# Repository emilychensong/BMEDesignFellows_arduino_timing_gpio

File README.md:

# Lab: EDA - Arduino Nano Every with LED and Button

## Fork Git Repository

1. Fork this GitLab repository into your userspace.
1. Add Dr. Palmeri (`mlp6`) as a Maintainer of your forked repository.  He will add the TAs and graders as Developers to this project for you.
1. Clone your version of the repository to your local computer.
1. Take note of:
    - The contents of [.gitignore](.gitignore) to exclude files that KiCad will create that should *not* be included in the git repository.
    - The existence of a `.gitlab-ci.yml` file to automatically build and test your project.
    - The existence of files for a KiCad project.

## Modify the Schematic

1. Update the schematic metadata with your name and add a fun logo.
1. Move the battery off-board and connect it to the `VIN` and `GND` pins on the Arduino Nano Every with a 2-pin socket connector.
1. Exclude the battery (`BT1`), the push buttont swith (`SW1`), and the LED (`D1`), along with all of their directly-connected socket connectors from the schematic (leave the pin connectors on the board).
1. Add a second `EYE` LED driven by the same `LED_OUT` signal.
1. Add another LED driven by `D5` on a net called `NOSE_LED_OUT`.
1. Add 4 mounting holes that can accomodate M3 bolts to your schematic that are not electrically connected.
1. Make sure that your schematic passes ERC.
1. Update the `Rev #` in the document metadata to `v1.1.0`.
1. Create a git commit of your modified schematic, give it an annotated tag of
`v1.1.0` and push it to your GitLab repository.
1. Upload a zip archive of your `v1.1.0` tagged repository to Gradescope.  You can download a zip of the repository on the Gitlab web interface with an option in the blue `Code` button.

## Add and SPICE Model an Analog Input

We will modulate an analog input to the `A0` pin of the Arduino Nano Every with
a potentiometer to allow a user to modulate the brightness of the LED.

1. On the `Inputs` sheet, add a potentiometer (`POT1`) with a 20 k$\Omega$
resistance and a fixed 10k$\Omega$ series resistance to create a voltage divider
of a `+5V` regulated output voltage from the Arduino Nano.
1. Connect the voltage across the potentiometer to the `A0` pin of the Arduino
Nano Every, with a Net Label called `BRIGHT_IN`.
1. Simulate the voltage on the `BRIGHT_IN` net for the minimum and maximum
resistance of `POT1`.
1. Is this voltage linear with changes in `POT1` resistance?
1. Adjust your fixed resistance to:
    - Ensure that the voltage on `BRIGHT_IN` never exceeds 3.3 V, and
    - Optimize the dynamic range of the potentiemeter to be as large as possible (i.e., make the slope of the voltage change as a function of resistance change as great as possible).
1. Include a screenshot of your final simulated `BRIGHT_IN` voltage in the `Inputs` schematic sheet.
1. Update the `Rev #` in the document metadata to `v1.2.0`.
1. Commit your updated schematic with the model and its results and tag it `v1.2.0`.
1. Push your commits and annotated tags to your GitLab repository.
1. Upload a zip archive of your `v1.2.0` tagged repository to Gradescope.

## Layout a Single-Sided PCB

Next you will create a PCB from the schematic that you captured last week.

1. Assign footprints to all parts in your schematic.
    - All resistors and capacitors and other passive components should be THT.
    - Your pins and sockets should be 2.54 mm vertical orientation (`Pin Socket:1x02,P2.54mm,Vertical`) to allow external wires to be attached to your PCB.
1. The **Design Rules** (`*.kicad_dru`) file in the repository will impose these constraints:
    - Trace width $\geq$ 20 mil
    - Clearance $\geq$ 32 mil
    - Drill diameter $\geq$ 1 mm
1. Set your **Page Settings** for the sheet footer metadata.
1. Your board should be single-sided.
1. Optimize the size of your board to be as small as possible in your layout (as outlined with `Edge.Cuts`).
1. Place mounting holes on each corner of the board, no closer than 2 mm to any edge.
1. Remember that THT component bodies should be on the *opposite* side of the board from their traces (in contrast to SMD components).
1. Use filled ground pours where possible.
1. Make sure that your schematic passes the **Design Rules Check (DRC)**.
1. Commit your PCB layout to your repository and tag it `v1.3.0`.
1. Push your commits and annotated tags to your GitLab repository.
1. Upload a zip archive of your `v1.2.0` tagged repository to Gradescope.

## What to Submit

- Make sure that all of your local git repository commits and annotated tags
have been pushed to GitLab.
- Make sure that Dr. Palmeri and the TAs are Maintainers of your forked
repository.
- Upload a zip archives of your tagged repository to Gradescope for each section
of this lab.

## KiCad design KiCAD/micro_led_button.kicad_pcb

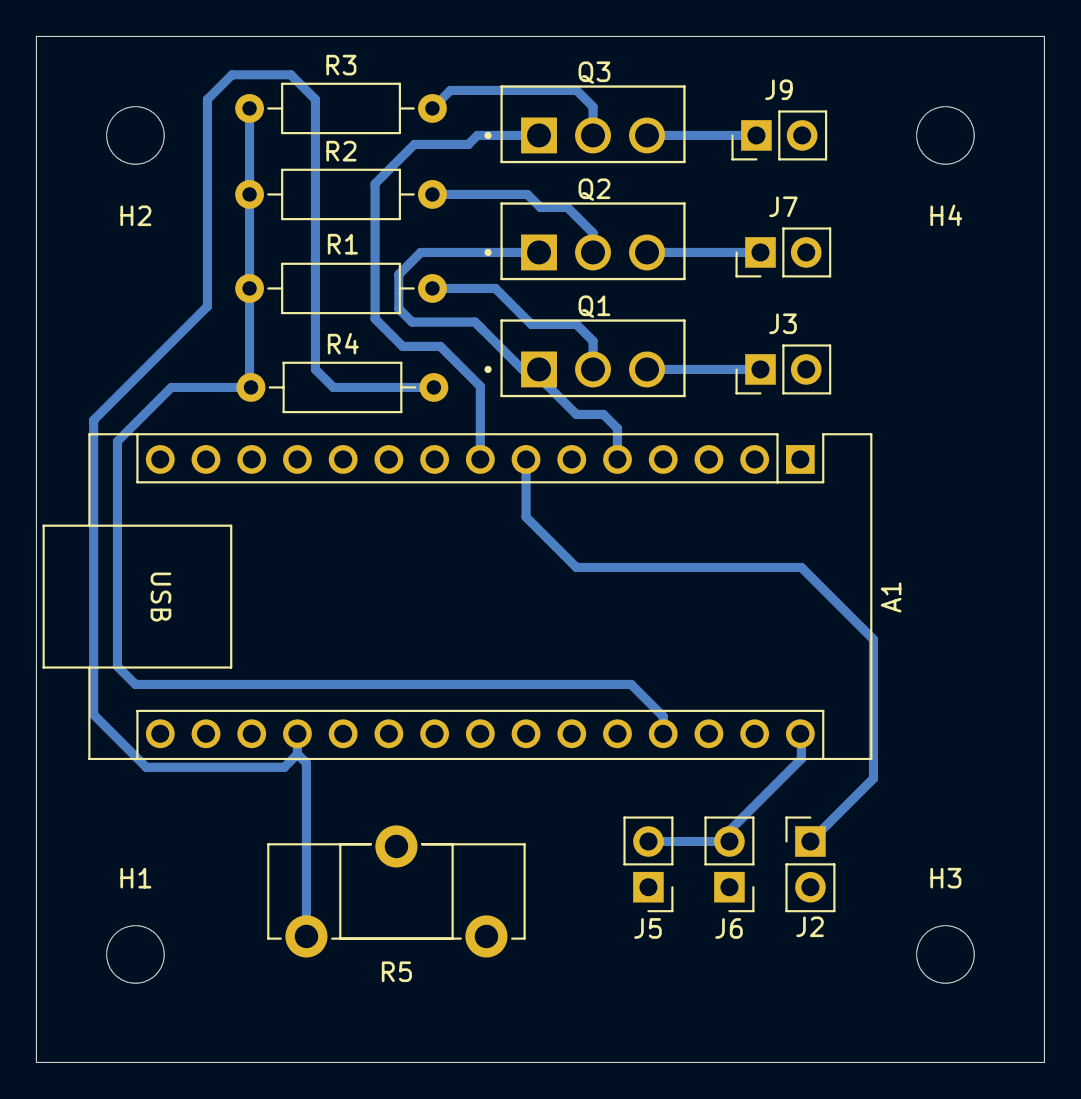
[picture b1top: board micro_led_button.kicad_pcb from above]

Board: 2 copper layers, 56.0 x 57.0 mm, 19 parts (0 on the bottom side), 13 nets.

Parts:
A1: Arduino_Nano_Every; Arduino_Nano
H1, H2, H3, H4: MountingHole; MountingHole_3.2mm_M3
J2, J3, J5, J7, J9: Conn_01x02_Pin; PinHeader_1x02_P2.54mm_Vertical
J6: Conn_01x02_Socket; PinHeader_1x02_P2.54mm_Vertical
Q1, Q2, Q3: IRFZ44N; TO254P1016X419X2286-3
R1, R2, R3: 1k; R_Axial_DIN0207_L6.3mm_D2.5mm_P10.16mm_Horizontal
R4: 10k; R_Axial_DIN0207_L6.3mm_D2.5mm_P10.16mm_Horizontal
R5: 20k; Potentiometer_ACP_CA14-H5_Horizontal

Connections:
+5V: A1.27 (+5V), R1.1, R2.1, R3.1, R4.1
+9V: A1.30 (VIN), J5.2, J6.2
/BRIGHT_IN: A1.19 (A0), R4.2, R5.1
/LED_OUT: A1.5 (D2), Q1.1, Q2.1
/NOSE_LED_OUT: A1.8 (D5), Q3.1
/TRIGGER: A1.7 (D4), J2.1
/leds/EYE1: J3.1, Q1.3
/leds/EYE2: J7.1, Q2.3
/leds/NOSE: J9.1, Q3.3
GND: A1.4 (GND), A1.29 (GND), J2.2, J3.2, J5.1, J6.1, J7.2, J9.2, R5.2
unnamed: Q1.2, R1.2
unnamed: Q2.2, R2.2
unnamed: Q3.2, R3.2
